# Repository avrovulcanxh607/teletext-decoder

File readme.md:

# Teletext In Vision Decoder Board

This repo is an attempt to open-source my teletext decoder.

It was originally designed, tested, and even a few were sold by me in 2019.

You can see the [original product page for it on my website](https://www.nathanmediaservices.co.uk/invision/).

You are now free to do whatever you like with this design and the firmware for it - except selling it. You are **expressly forbidden** to use these designs to create a product that you then go on to resell, unless I have given you written permission otherwise.

Disclaimer: the design and firmwares are offered completely as-is, with no warranty of any kind. I will no longer be offering support or assistance on this project, if you want to build one you must figure it out from the resources provided here. 

## Why are there so many different firmwares?

Because I have built various slightly different boards into different projects and cases for different purposes, and with different ancillaries. For example, there are code bases here which support LCD screens, IR remotes, thumbwheel selectors, serial remotes, etc. You'll probably need to try a few and modify them to suit your needs.

## PCB Versions
There are three total versions of the decoder PCB. The first version was a prototype, and features a number of mistakes - I therefore do not recommend using it. Unless you're a complete masochist.

The first revision fixes the mistakes on the prototype and is ready to use. 

The second revision swaps the Arduino Nano for a standalone ATMega328(p) chip. This makes it cheaper and easier for manufacture, but harder for programming/debugging - therefore I don't recommend this revision for the novice.

## Notes
Depending on how you configure the ATMega328(p) in revision 2, you may omit the crystal Y2 and associated tuning capacitors.

You may also omit R17 and R18 - these are I2C pullup resistors, and I have yet to find a need for more pullup than already onboard the microcontroller.

You need not install the output circuitry for the S-Video or RGB outputs if you don't need those - on the other hand, if you only intend to use the RGB output you can probably get rid of the entire PAL coder circuit and just bridge the chip's RGB directly to the outputs.

Really, you only actually *need* the teletext decoder, video input circuitry, and the microcontroller - the rest depends on what you're using it for! I have shipped some very bare boards in specific circumstances!

Similarly, the board is designed to take a 9-15v DC input and regulate it down to 5v for operation - however, the LM7805 should really have a heatsink and can be unreliable. Personally I always bridge the regulator out and supply 5v directly from an external supply.

If you are having trouble getting colour to work on the PAL CVBS or S-Video outputs, you need to check the colour subcarrier frequency. Your crystal may require slightly different tuning capacitors. However I have found most TVs to be very forgiving of the subcarrier frequency.

If you do decide to do something cool with this design, please consider posting photos of it to Bluesky and tagging "@nmsni.co.uk", I would love to see it!

Also... consider kicking a quid or two my way at [Ko-Fi](https://ko-fi.com/avrovulcanxh607). It took a fair bit of time to figure this out.

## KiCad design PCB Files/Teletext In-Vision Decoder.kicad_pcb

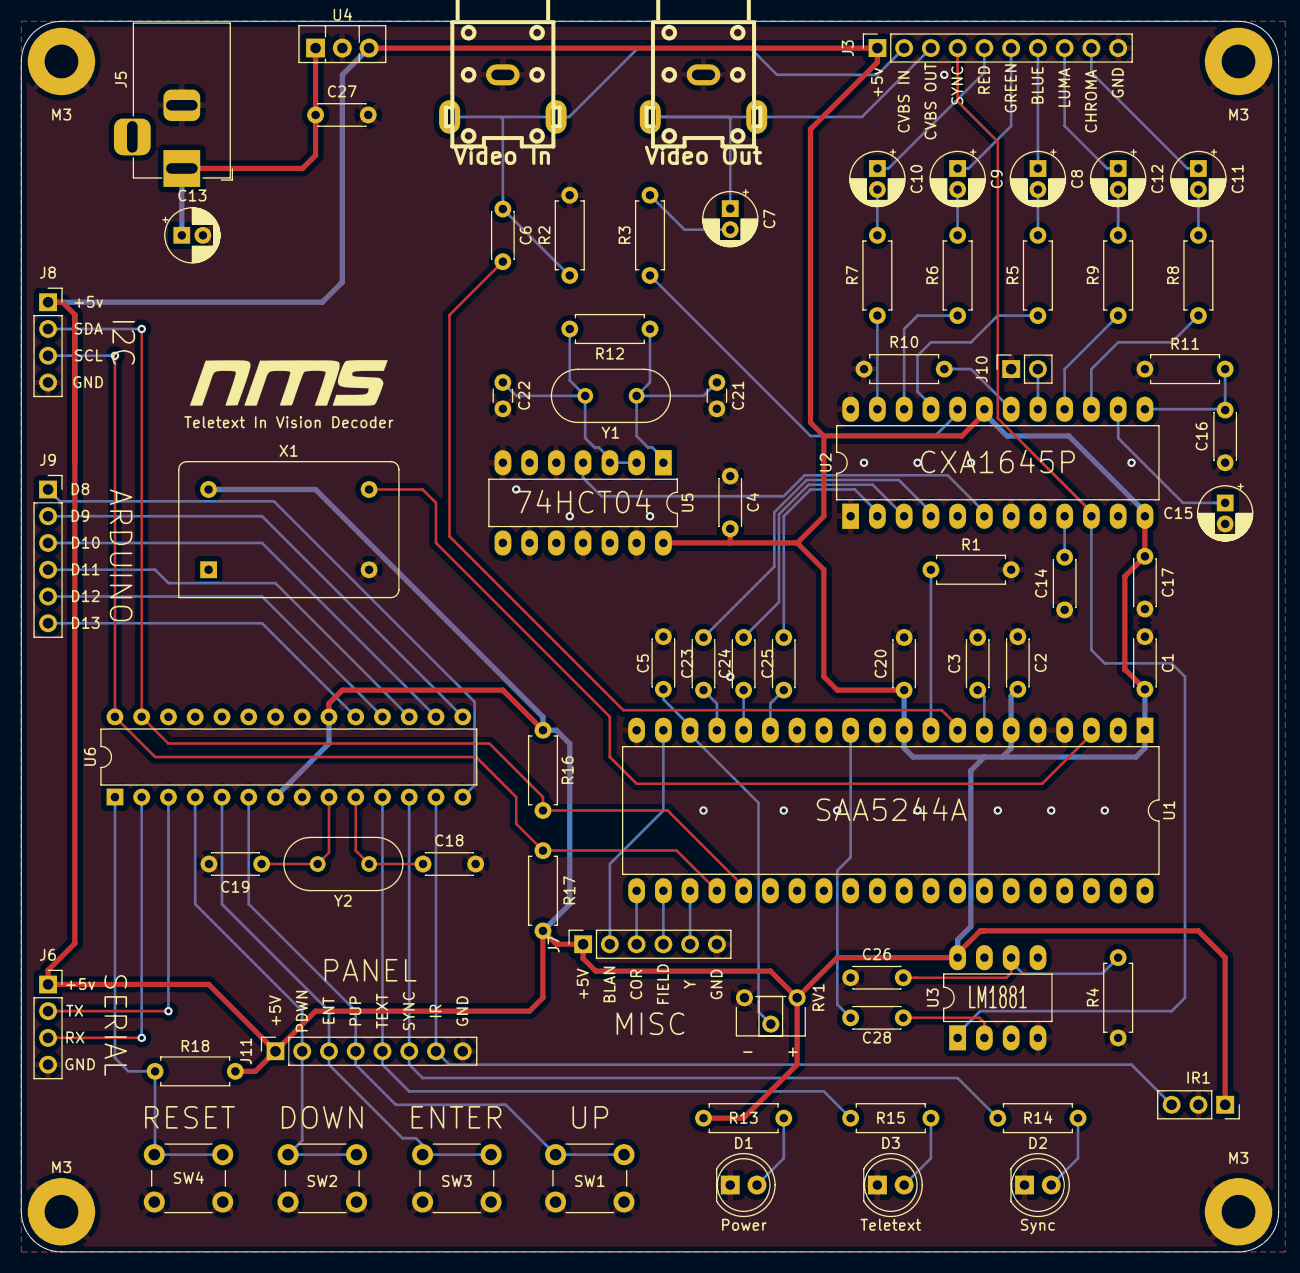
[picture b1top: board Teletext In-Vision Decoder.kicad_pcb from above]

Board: 2 copper layers, 119.4 x 116.8 mm, 78 parts (0 on the bottom side), 71 nets.

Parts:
C1, C2, C3, C4, C5, C6, C14, C16, C17, C20, C23, C24, C25, C27, C28: 100nF; C_Disc_D4.3mm_W1.9mm_P5.00mm
C7, C8, C9, C10, C11, C12: 220uF; CP_Radial_D5.0mm_P2.00mm
C13, C15: 10uF; CP_Radial_D5.0mm_P2.00mm
C18, C19: C; C_Disc_D4.3mm_W1.9mm_P5.00mm
C21, C22: 33pF; C_Disc_D3.0mm_W1.6mm_P2.50mm
C26: 100nf; C_Disc_D4.3mm_W1.9mm_P5.00mm
D1: POWER; LED_D5.0mm
D2: SYNC; LED_D5.0mm
D3: TEXT; LED_D5.0mm
IR1: IR Receiver; PinSocket_1x03_P2.54mm_Vertical
J1: Video In; rca_yellow
J2: Video Out; rca_yellow
J3: VIDEO; PinSocket_1x10_P2.54mm_Vertical
J5: POWER IN; BarrelJack_Horizontal
J6: SERIAL; PinSocket_1x04_P2.54mm_Vertical
J7: MISC; PinSocket_1x06_P2.54mm_Vertical
J8: I2C; PinSocket_1x04_P2.54mm_Vertical
J9: ARDUINO; PinSocket_1x06_P2.54mm_Vertical
J10: Y TRAP; PinSocket_1x02_P2.54mm_Vertical
J11: PANEL; PinSocket_1x08_P2.54mm_Vertical
M3, M3#2, M3#3, M3#4: MountingHole_3.2mm_M3_Pad
R1: 27k; R_Axial_DIN0207_L6.3mm_D2.5mm_P7.62mm_Horizontal
R2, R3, R5, R6, R7, R8, R9: 75R; R_Axial_DIN0207_L6.3mm_D2.5mm_P7.62mm_Horizontal
R4: 680k; R_Axial_DIN0207_L6.3mm_D2.5mm_P7.62mm_Horizontal
R10: 16k; R_Axial_DIN0207_L6.3mm_D2.5mm_P7.62mm_Horizontal
R11: 47k; R_Axial_DIN0207_L6.3mm_D2.5mm_P7.62mm_Horizontal
R12: 4.7M; R_Axial_DIN0207_L6.3mm_D2.5mm_P7.62mm_Horizontal
R13, R14, R15: 1k; R_Axial_DIN0207_L6.3mm_D2.5mm_P7.62mm_Horizontal
R16, R17: 10k; R_Axial_DIN0207_L6.3mm_D2.5mm_P7.62mm_Horizontal
R18: R; R_Axial_DIN0207_L6.3mm_D2.5mm_P7.62mm_Horizontal
RV1: 10k; Potentiometer_ACP_CA6-H2,5_Horizontal
SW1: PUP; SW_PUSH_6mm
SW2: PDWN; SW_PUSH_6mm
SW3: ENTER; SW_PUSH_6mm
SW4: SW_Push; SW_PUSH_6mm
U1: SAA5244A; DIP-40_W15.24mm_LongPads
U2: CXA1645P; DIP-24_W10.16mm_LongPads
U3: LM1881; DIP-8_W7.62mm_LongPads
U4: L7805; TO-126-3_Vertical
U5: 74HCT04; DIP-14_W7.62mm_LongPads
U6: ATmega328-P; DIP-28_W7.62mm
X1: CXO_DIP14; Oscillator_DIP-14
Y1: 4.43 MHz; Crystal_HC49-U_Vertical
Y2: Crystal; Crystal_HC49-U_Vertical

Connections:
4.43MHz: U2.6 (SCIN), U5.4
27MHz: U1.3 (OSCIN), X1.8 (OUT)
+5V: C1.2, C2.2, C4.2, C17.1, C20.1, IR1.1, J3.1, J6.1, J7.1, J8.1, J11.1, R13.2, R16.1, R17.1, R18.2, RV1.1, U1.1 (VDD), U1.6 (REF+), U1.10 (VDD), U2.12 (VCC), U2.19 (VCC), U3.8 (VCC), U4.3 (OUT), U5.14 (VCC), U6.7 (VCC), U6.20 (AVCC), X1.14 (Vcc)
B: C23.1, U1.17 (B)
BLAN: J7.2, U1.19 (BLAN)
BLUE: C8.1, J3.7
BOUT: R5.1, U2.21 (BOUT)
CHROMA: C11.1, J3.9
COR: J7.3, U1.21 (COR)
COUT: R8.1, U2.15 (COUT)
CVBS: C7.1, J2.1 (In), J3.3
CVBSin: C6.1, J1.1 (In), J3.2, R2.1
CVOUT: R3.1, U2.20 (CVOUT)
ENTER: J11.3, SW3.1, U6.5 (PD3)
G: C24.1, U1.16 (G)
GND: C1.1, C2.1, C3.2, C4.1, C5.1, C13.2, C14.1, C15.2, C16.1, C17.2, C18.2, C19.2, C20.2, C21.2, C22.2, C26.1, C27.2, D1.1 (K), D2.1 (K), D3.1 (K), IR1.2, J1.2 (Ext), J2.2 (Ext), J3.10, J5.2, J6.4, J7.6, J8.4, J10.1, J11.8, M3.1, M3#2.1, M3#3.1, M3#4.1, R1.2, R2.2, R4.1, R10.2, R11.1, RV1.3, SW1.2, SW2.2, SW3.2, SW4.2, U1.4 (OSCGND), U1.5 (VSS), U1.11 (POL), U1.14 (VSS), U1.20 (VSS), U2.1 (GND), U2.7 (NPIN), U2.24 (GND), U3.4 (GND), U4.2 (GND), U5.5, U5.7 (GND), U5.9, U5.11, U5.13, U6.8 (GND), U6.22 (GND), X1.7 (GND)
GOUT: R6.1, U2.22 (GOUT)
GREEN: C9.1, J3.6
IR: IR1.3, J11.7, U6.13 (PD7)
LFB: C28.1, U1.12 (STTV/LFB)
LUMA: C12.1, J3.8
unnamed: C3.1, U1.7 (BLACK)
unnamed: C5.2, RV1.2, U1.18 (RGBREF)
unnamed: C7.2, R3.2
unnamed: C8.2, R5.2
unnamed: C9.2, R6.2
unnamed: C10.2, R7.2
unnamed: C11.2, R8.2
unnamed: C12.2, R9.2
unnamed: C14.2, U2.9 (YCLPC)
unnamed: C15.1, U2.14 (VREF)
unnamed: C16.2, R11.2, U2.13 (IREF)
unnamed: C18.1, U6.10 (XTAL2/PB7), Y2.1
unnamed: C19.1, U6.9 (XTAL1/PB6), Y2.2
unnamed: C21.1, R12.1, U5.1, Y1.1
unnamed: C22.1, R12.2, U5.2, U5.3, Y1.2
unnamed: C23.2, U2.4 (BIN)
unnamed: C24.2, U2.3 (GIN)
unnamed: C25.2, U2.2 (RIN)
unnamed: C26.2, R4.2, U3.6 (INT)
unnamed: C28.2, U3.2 (VIDEO)
unnamed: D1.2 (A), R13.1
unnamed: D2.2 (A), R14.1
unnamed: D3.2 (A), R15.1
unnamed: J10.2, U2.17 (YTRAP)
unnamed: R1.1, U1.9 (IREF)
unnamed: R10.1, U2.18 (FO)
unnamed: R18.1, SW4.1, U6.1 (~RESET/PC6)
unnamed: J9.1, U6.14 (PB0)
unnamed: J9.2, U6.15 (PB1)
unnamed: J9.3, U6.16 (PB2)
unnamed: J9.4, U6.17 (PB3)
unnamed: J9.5, U6.18 (PB4)
unnamed: J9.6, U6.19 (PB5)
ODDEVEN: J7.4, U1.22 (ODD/EVEN)
PDWN: J11.2, SW2.1, U6.4 (PD2)
PUP: J11.4, SW1.1, U6.6 (PD4)
R: C25.1, U1.15 (R)
RED: C10.1, J3.5
ROUT: R7.1, U2.23 (ROUT)
RX: J6.3, U6.2 (PD0)
SCL: J8.3, R17.2, U1.24 (SCL), U6.28 (PC5)
SDA: J8.2, R16.2, U1.25 (SDA), U6.27 (PC4)
SYNC: J3.4, U2.10 (SYNC_IN), U3.1 (CSYNC)
SYNCOK: J11.6, R14.2, U6.12 (PD6)
TEXTOK: J11.5, R15.2, U6.11 (PD5)
TX: J6.2, U6.3 (PD1)
VIDEO_IN: C6.2, U1.8 (CVBS)
VIN: C13.1, C27.1, J5.1, U4.1 (IN)
Y: J7.5, U1.23 (Y)
YOUT: R9.1, U2.16 (YOUT)

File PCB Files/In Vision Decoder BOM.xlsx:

ref | value5 | footprint | part | description | names | tstamps6 | tstamp | datasheet | lib7 | part8 | alias | description9 | docs | fp | field | name10 | num | name11 | type | logical | uri | code | name12 | ref13 | pin
C1 | 100nF | Capacitor_THT:C_Disc_D3.0mm_W1.6mm_P2.50mm | C | Unpolarized capacitor
C14 | 100nF | Capacitor_THT:C_Disc_D3.0mm_W1.6mm_P2.50mm | C | Unpolarized capacitor
C16 | 100nF | Capacitor_THT:C_Disc_D3.0mm_W1.6mm_P2.50mm | C | Unpolarized capacitor
C17 | 100nF | Capacitor_THT:C_Disc_D3.0mm_W1.6mm_P2.50mm | C | Unpolarized capacitor
C2 | 100nF | Capacitor_THT:C_Disc_D3.0mm_W1.6mm_P2.50mm | C | Unpolarized capacitor
C20 | 100nF | Capacitor_THT:C_Disc_D3.0mm_W1.6mm_P2.50mm | C | Unpolarized capacitor
C23 | 100nF | Capacitor_THT:C_Disc_D3.0mm_W1.6mm_P2.50mm | C | Unpolarized capacitor
C24 | 100nF | Capacitor_THT:C_Disc_D3.0mm_W1.6mm_P2.50mm | C | Unpolarized capacitor
C25 | 100nF | Capacitor_THT:C_Disc_D3.0mm_W1.6mm_P2.50mm | C | Unpolarized capacitor
C26 | 100nf | Capacitor_THT:C_Disc_D3.0mm_W1.6mm_P2.50mm | C | Unpolarized capacitor
C27 | 100nF | Capacitor_THT:C_Disc_D3.0mm_W1.6mm_P2.50mm | C | Unpolarized capacitor
C3 | 100nF | Capacitor_THT:C_Disc_D3.0mm_W1.6mm_P2.50mm | C | Unpolarized capacitor
C4 | 100nF | Capacitor_THT:C_Disc_D3.0mm_W1.6mm_P2.50mm | C | Unpolarized capacitor
C5 | 100nF | Capacitor_THT:C_Disc_D3.0mm_W1.6mm_P2.50mm | C | Unpolarized capacitor
C6 | 100nF | Capacitor_THT:C_Disc_D3.0mm_W1.6mm_P2.50mm | C | Unpolarized capacitor
R16 | 10k | Resistor_THT:R_Axial_DIN0207_L6.3mm_D2.5mm_P7.62mm_Horizontal | R | Resistor
R17 | 10k | Resistor_THT:R_Axial_DIN0207_L6.3mm_D2.5mm_P7.62mm_Horizontal | R | Resistor
RV1 | 10k | Potentiometer_THT:Potentiometer_ACP_CA6-H2,5_Horizontal | R_POT | Potentiometer
C13 | 10uF | Capacitor_THT:CP_Radial_D5.0mm_P2.00mm | CP | Polarized capacitor
C15 | 10uF | Capacitor_THT:CP_Radial_D5.0mm_P2.00mm | CP | Polarized capacitor
R10 | 16k | Resistor_THT:R_Axial_DIN0207_L6.3mm_D2.5mm_P7.62mm_Horizontal | R | Resistor
R13 | 1k | Resistor_THT:R_Axial_DIN0207_L6.3mm_D2.5mm_P7.62mm_Horizontal | R | Resistor
R14 | 1k | Resistor_THT:R_Axial_DIN0207_L6.3mm_D2.5mm_P7.62mm_Horizontal | R | Resistor
R15 | 1k | Resistor_THT:R_Axial_DIN0207_L6.3mm_D2.5mm_P7.62mm_Horizontal | R | Resistor
C10 | 220uF | Capacitor_THT:CP_Radial_D5.0mm_P2.00mm | CP | Polarized capacitor
C11 | 220uF | Capacitor_THT:CP_Radial_D5.0mm_P2.00mm | CP | Polarized capacitor
C12 | 220uF | Capacitor_THT:CP_Radial_D5.0mm_P2.00mm | CP | Polarized capacitor
C7 | 220uF | Capacitor_THT:CP_Radial_D5.0mm_P2.00mm | CP | Polarized capacitor
C8 | 220uF | Capacitor_THT:CP_Radial_D5.0mm_P2.00mm | CP | Polarized capacitor
C9 | 220uF | Capacitor_THT:CP_Radial_D5.0mm_P2.00mm | CP | Polarized capacitor
R1 | 27k | Resistor_THT:R_Axial_DIN0207_L6.3mm_D2.5mm_P7.62mm_Horizontal | R | Resistor
C21 | 33pF | Capacitor_THT:C_Disc_D3.0mm_W1.6mm_P2.50mm | C | Unpolarized capacitor
C22 | 33pF | Capacitor_THT:C_Disc_D3.0mm_W1.6mm_P2.50mm | C | Unpolarized capacitor
Y1 | 4.43 MHz | Crystal:Crystal_HC49-U_Vertical | Crystal | Two pin crystal
R12 | 4.7M | Resistor_THT:R_Axial_DIN0207_L6.3mm_D2.5mm_P7.62mm_Horizontal | R | Resistor
R11 | 47k | Resistor_THT:R_Axial_DIN0207_L6.3mm_D2.5mm_P7.62mm_Horizontal | R | Resistor
R4 | 680k | Resistor_THT:R_Axial_DIN0207_L6.3mm_D2.5mm_P7.62mm_Horizontal | R | Resistor
U5 | 74HCT04 | Package_DIP:DIP-14_W7.62mm_LongPads | 74HCT04 | Hex Inverter
R2 | 75R | Resistor_THT:R_Axial_DIN0207_L6.3mm_D2.5mm_P7.62mm_Horizontal | R | Resistor
R3 | 75R | Resistor_THT:R_Axial_DIN0207_L6.3mm_D2.5mm_P7.62mm_Horizontal | R | Resistor
R5 | 75R | Resistor_THT:R_Axial_DIN0207_L6.3mm_D2.5mm_P7.62mm_Horizontal | R | Resistor
R6 | 75R | Resistor_THT:R_Axial_DIN0207_L6.3mm_D2.5mm_P7.62mm_Horizontal | R | Resistor
R7 | 75R | Resistor_THT:R_Axial_DIN0207_L6.3mm_D2.5mm_P7.62mm_Horizontal | R | Resistor
R8 | 75R | Resistor_THT:R_Axial_DIN0207_L6.3mm_D2.5mm_P7.62mm_Horizontal | R | Resistor
R9 | 75R | Resistor_THT:R_Axial_DIN0207_L6.3mm_D2.5mm_P7.62mm_Horizontal | R | Resistor
J9 | ARDUINO | Connector_PinSocket_2.54mm:PinSocket_1x06_P2.54mm_Vertical | Conn_01x06_Male
A1 | Arduino_Nano_v3.x | Module:Arduino_Nano | Arduino_Nano_v3.x | Arduino Nano v3.x
U2 | CXA1645P | Package_DIP:DIP-24_W10.16mm_LongPads | CXA1645P
X1 | CXO_DIP14 | Oscillator:Oscillator_DIP-14 | CXO_DIP14 | Crystal Clock Oscillator, DIP14-style metal package
SW3 | ENTER | Button_Switch_THT:SW_PUSH_6mm | SW_Push | Push button switch, generic, two pins
J8 | I2C | Connector_PinSocket_2.54mm:PinSocket_1x04_P2.54mm_Vertical | Conn_01x04_Male
IR1 | IR Receiver | Connector_PinSocket_2.54mm:PinSocket_1x03_P2.54mm_Vertical | Conn_01x03_Male
U4 | L7805 | Package_TO_SOT_THT:TO-126-3_Vertical | L7805 | Positive 1.5A 35V Linear Regulator, Fixed Output 5V, TO-220/TO-263/TO-252
U3 | LM1881 | Package_DIP:DIP-8_W7.62mm_LongPads | LM1881
J7 | MISC | Connector_PinSocket_2.54mm:PinSocket_1x06_P2.54mm_Vertical | Conn_01x06_Male
J11 | PANEL | Connector_PinSocket_2.54mm:PinSocket_1x08_P2.54mm_Vertical | Conn_01x08_Male
SW2 | PDWN | Button_Switch_THT:SW_PUSH_6mm | SW_Push | Push button switch, generic, two pins
D1 | POWER | LED_THT:LED_D5.0mm | LED | Light emitting diode
J5 | POWER IN | Connector_BarrelJack:BarrelJack_Horizontal | Barrel_Jack_MountingPin | DC Barrel Jack with a mounting pin
SW1 | PUP | Button_Switch_THT:SW_PUSH_6mm | SW_Push | Push button switch, generic, two pins
U1 | SAA5244A | Package_DIP:DIP-40_W15.24mm_LongPads | SAA5244A
J6 | SERIAL | Connector_PinSocket_2.54mm:PinSocket_1x04_P2.54mm_Vertical | Conn_01x04_Male
D2 | SYNC | LED_THT:LED_D5.0mm | LED | Light emitting diode
D3 | TEXT | LED_THT:LED_D5.0mm | LED | Light emitting diode
J3 | VIDEO | Connector_PinSocket_2.54mm:PinSocket_1x10_P2.54mm_Vertical | Conn_01x10_Male
J1 | Video In | AV Connectors:rca_yellow | Conn_Coaxial | coaxial connector (BNC, SMA, SMB, SMC, Cinch/RCA, ...)
J2 | Video Out | AV Connectors:rca_yellow | Conn_Coaxial | coaxial connector (BNC, SMA, SMB, SMC, Cinch/RCA, ...)
J10 | Y TRAP | Connector_PinSocket_2.54mm:PinSocket_1x02_P2.54mm_Vertical | Conn_01x02_Male

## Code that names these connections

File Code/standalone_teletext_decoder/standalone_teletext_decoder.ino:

// Teletext In-Vision Decoder
// Nathan Media Services, (c) 2023
// V2.0 ALPHA

#include <Wire.h>
#include <EEPROM.h>

int selected_page[3] = {1,0,0};
int thumbwheel[3] = {1,5,2};

const int TextOK = 5;
const int SyncOK = 6;

const byte colourBars[] = {
  0x1d,0x20,0x20,0x20,0x03,0x1d,0x20,0x20,0x20,
  0x20,0x06,0x1d,0x20,0x20,0x20,0x20,0x02,0x1d,
  0x20,0x20,0x20,0x20,0x05,0x1d,0x20,0x20,0x20,
  0x20,0x01,0x1d,0x20,0x20,0x20,0x20,0x04,0x1d,
  0x20,0x20,0x20,0x20
};

const byte splashIdent[] = {
  0x17,0x1c,0x20,0x20,0x7c,0x7c,0x7c,0x7c,0x20,
  0x7c,0x7c,0x7c,0x7c,0x7c,0x7c,0x20,0x7c,0x7c,
  0x7c,0x7c,0x01,0x1d,0x17,0x1c,0x20,0x6a,0x35,
  0x20,0x6a,0x35,0x6a,0x35,0x20,0x7f,0x20,0x6a,
  0x35,0x6a,0x7d,0x7c,0x7c,0x34,0x01,0x1d,0x17,
  0x1c,0x20,0x7f,0x20,0x20,0x7f,0x20,0x7f,0x20,
  0x6a,0x35,0x20,0x7f,0x20,0x7c,0x7c,0x7c,0x3f,
  0x20,0x01,0x1d,0x14,0x1c,0x20,0x2c,0x20,0x20,
  0x2c,0x20,0x2c,0x20,0x28,0x24,0x20,0x2c,0x20,
  0x2c,0x2c,0x2c,0x24,0x20,0x01,0x1d,0x06,0x1c,
  0x20,0x54,0x65,0x6c,0x65,0x74,0x65,0x78,0x74,
  0x20,0x44,0x65,0x63,0x6f,0x64,0x65,0x72,0x20,
  0x01,0x1d  
};

int i2c_registers[9] = {
  0x00, // 0
  0x14, // 1
  0x00, // 2
  0x00, // 3
  0x00, // 4 (ignored)
  0xcf, // 5
  0x55, // 6
  0x07, // 7
};

void readThumbwheel() {
  digitalWrite(8,LOW);
  digitalWrite(9,HIGH);
  digitalWrite(10,HIGH);

  thumbwheel[0] = (15-((digitalRead(11)*1) + (digitalRead(12)*2) + (digitalRead(13)*4) + (digitalRead(PD2)*8)));

  delay(10);

  digitalWrite(8,HIGH);
  digitalWrite(9,LOW);
  digitalWrite(10,HIGH);

  thumbwheel[1] = (15-((digitalRead(11)*1) + (digitalRead(12)*2) + (digitalRead(13)*4) + (digitalRead(PD2)*8)));

  delay(10);
  
  digitalWrite(8,HIGH);
  digitalWrite(9,HIGH);
  digitalWrite(10,LOW);

  thumbwheel[2] = (15-((digitalRead(11)*1) + (digitalRead(12)*2) + (digitalRead(13)*4) + (digitalRead(PD2)*8)));
}

void setup() {
  Serial.begin(9600);
  Serial.println("NMS-INV-2000-V2.0-ALPHA");
  
  pinMode(TextOK, OUTPUT);
  pinMode(SyncOK, OUTPUT);
  pinMode(PD4, OUTPUT);

  pinMode(8, OUTPUT);
  pinMode(9, OUTPUT);
  pinMode(10, OUTPUT);
  
  pinMode(11, INPUT_PULLUP);
  pinMode(12, INPUT_PULLUP);
  pinMode(13, INPUT_PULLUP);
  pinMode(PD2, INPUT_PULLUP);

  Wire.begin();
  Wire.setClock(100000);
  
  for (int address=0; address<=7; address++) {
    writeByte(address,i2c_registers[address]);
  }

  writeByte(12,0);
  writeByte(13,0);

  splashScreen();

  //bitSet(i2c_registers[0],7);
  //writeByte(0x00,i2c_registers[0]);

  digitalWrite(TextOK,HIGH);
  digitalWrite(SyncOK,HIGH);
  digitalWrite(PD4,HIGH);

  delay(1000);

  readThumbwheel();
  callPage(thumbwheel[0],thumbwheel[1],thumbwheel[2]);
}

void loop() {
  updateStatus();
  readThumbwheel();

  if(thumbwheel[0] != selected_page[0] || thumbwheel[1] != selected_page[1] || thumbwheel[2] != selected_page[2])
  {
    selected_page[0] = thumbwheel[0];
    selected_page[1] = thumbwheel[1];
    selected_page[2] = thumbwheel[2];

    Serial.print(thumbwheel[0]);
    Serial.print(thumbwheel[1]);
    Serial.print(thumbwheel[2]);
    Serial.println();
    
    callPage(thumbwheel[0],thumbwheel[1],thumbwheel[2]);
  }
}

void writeByte(int subAddress, int data)  // Write a Byte to the I2C IC
{
  Wire.beginTransmission(0x11);  // Initialize the Tx buffer
  Wire.write(subAddress);        // Put slave register address in Tx buffer
  Wire.write(data);              // Put data in Tx buffer
  Wire.endTransmission();        // Send the Tx buffer
}

int readByte(int subAddress)  // Read a Byte from the I2C IC
{
  Wire.beginTransmission(0x11);    // Get the slave's attention, tell it we're sending a command byte
  Wire.write(subAddress);          // The command byte, sets pointer to register with address of 0x32
  Wire.requestFrom(0x11,1);        // Tell slave we need to read 1byte from the current register
  int slaveByte2 = Wire.read();    // read that byte into 'slaveByte2' variable
  Wire.endTransmission();
  return slaveByte2;
}

void setCursor(int row, int column)
{
  writeByte(0x09,row); // row
  writeByte(0x0a,column+64); // column
}

void writeChar(char input)  // Write a Character to the Framebuffer
{
  bitClear(i2c_registers[0],0);  // Make sure we're writing to 11A not 11B
  writeByte(0x00,i2c_registers[0]);
  writeByte(0x0b,input);
}

void splashScreen(void)
{
  int i=0;
  setCursor(0,0);
  for (int l=0; l<25; l++)
  {
    for (i=0; i<40; i++)
    {
      writeByte(0x0b,colourBars[i]);
    }
  }

  for (int l=10; l<15; l++)
  {
    setCursor(l,9);

    for (i=(22 * (l - 10)); i<((22 * (l - 10))+22); i++)
    {
      writeByte(0x0b,splashIdent[i]);
    }
  }
}

void updateStatus()
{
  bitSet(i2c_registers[0],0);
  writeByte(0x00,i2c_registers[0]);
  digitalWrite(TextOK,bitRead(readByte(0x0b),1));

  digitalWrite(PD4,!bitRead(readByte(0x0b),0));

  bitClear(i2c_registers[0],0);  // Make sure we're reading 11A
  writeByte(0x00,i2c_registers[0]);
  setCursor(0x19,0x09);
  digitalWrite(SyncOK,!bitRead(readByte(0x0b),5));
}

bool callPage(int M, int T, int U)  // Calls a Page
{
  int pten,punit;
  pten=T+48;
  punit=U+48;
  
  if (T > 9)
    pten=T+55;
  if (U > 9)
    punit=U+55;

  bitClear(i2c_registers[0],0);  // Make sure we're writing to 11A not 11B
  writeByte(0x00,i2c_registers[0]);
  
  if (M < 9 && M > 0)
  {
    setCursor(0x00,0x00);
    
    //writeByte(0x0b,0x6a);
    //writeByte(0x0b,0x7a);
    
    writeByte(0x0b,0x07); // (space 0x07) (green 0x02)
    writeByte(0x0b,0x50); // P
    writeByte(0x0b,48+M); 
    writeByte(0x0b,pten); // Write the Page status on row 0
    writeByte(0x0b,punit);
    writeByte(0x0b,0x20);
    setCursor(0x00,0x02);
    
    if (M == 8)
    {
      M = 0;  // 8 becomes 0 because of binary stuff
    }
    
    writeByte(0x02,0x00);
    writeByte(0x03,24+M);
  
    writeByte(0x02,0x01);
    writeByte(0x03,16+T); // Write the page number to the register
  
    writeByte(0x02,0x02);
    writeByte(0x03,16+U);
    return true;
  }
  else  // If the value isn't valid, change the number red
  {
    setCursor(0x00,0x00);
    writeByte(0x0b,0x01); // red
    writeByte(0x0b,0x50); // P
    writeByte(0x0b,48+M); 
    writeByte(0x0b,pten); // Write the Page status on row 0
    writeByte(0x0b,punit);
    setCursor(0x00,0x02);
    return false;
  }
  
}

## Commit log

2025-02-14 pushed files
2025-02-14 update the readme
2026-01-15 Added more notes to Readme
